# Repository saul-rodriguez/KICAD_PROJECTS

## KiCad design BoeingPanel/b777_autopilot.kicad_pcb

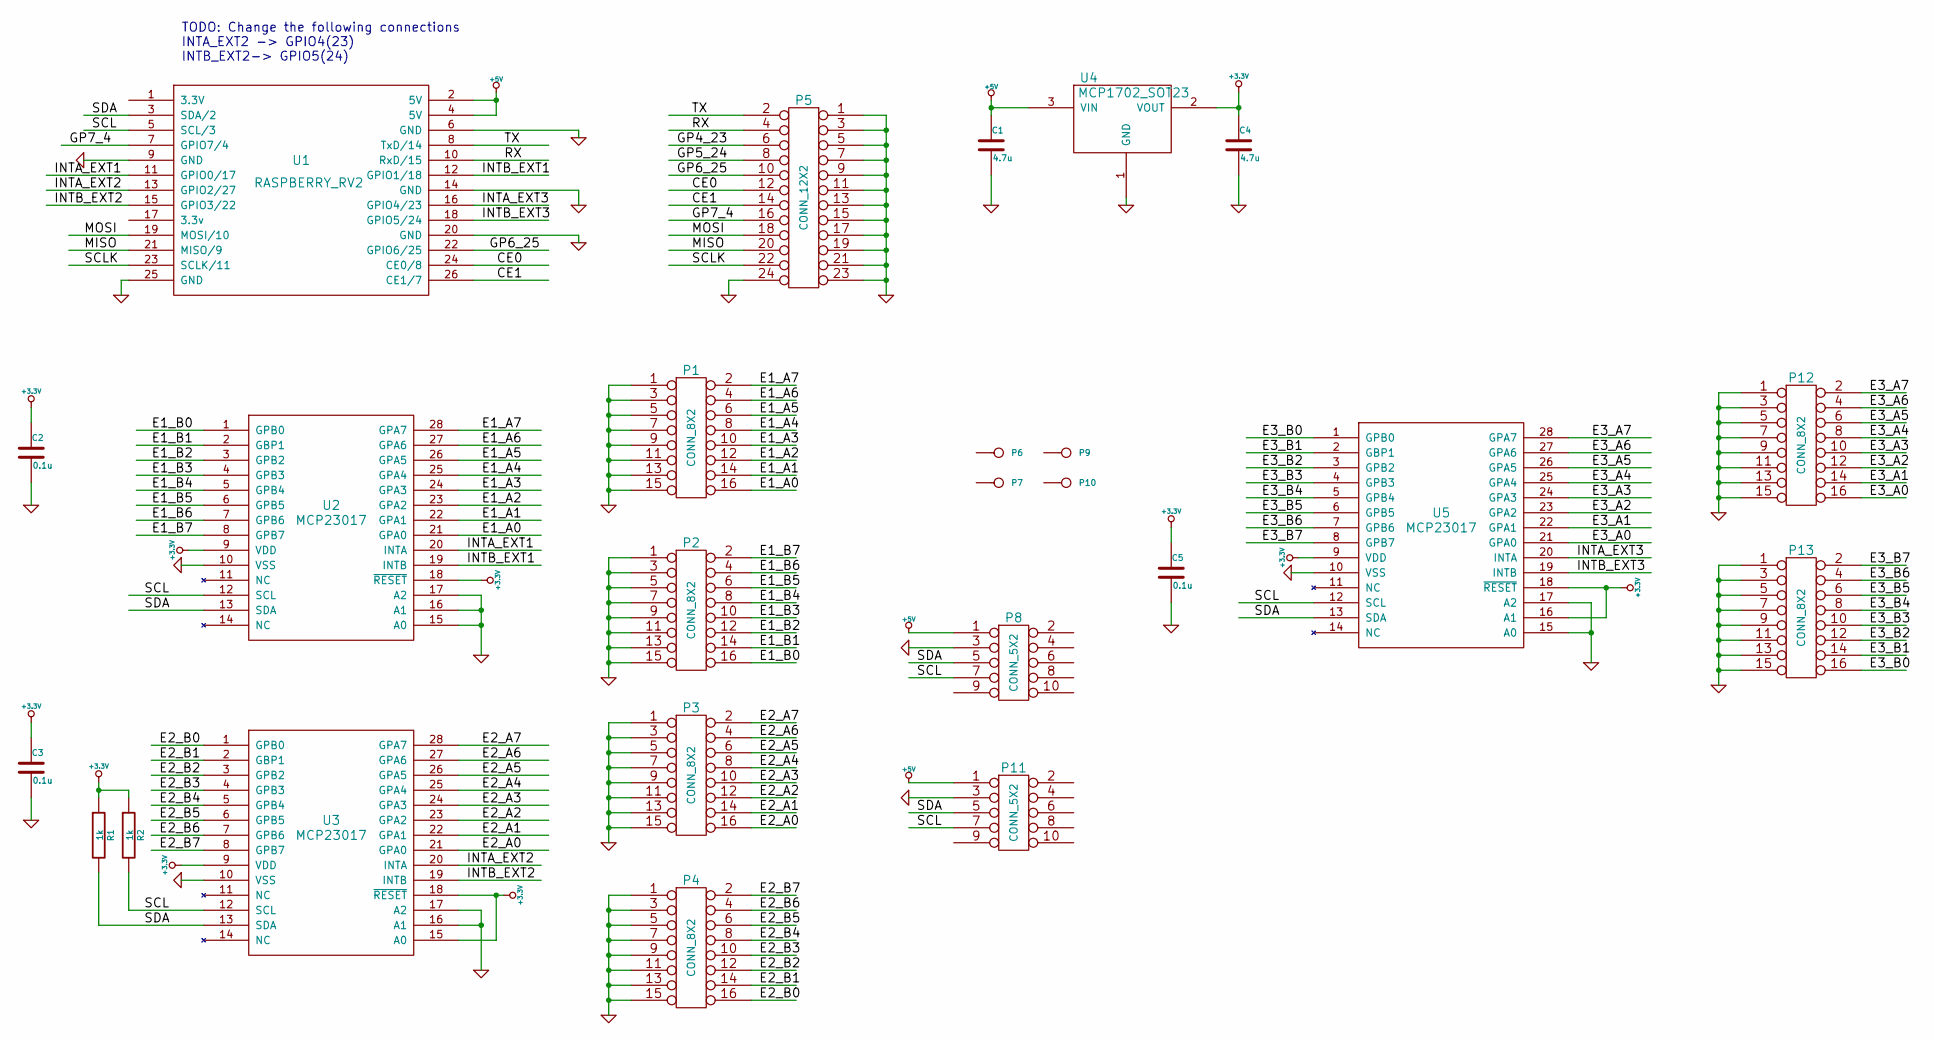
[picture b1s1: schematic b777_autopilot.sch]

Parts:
C1, C4: 4.7u
C2, C3, C5: 0.1u
P1, P2, P3, P4, P12, P13: CONN_8X2
P5: CONN_12X2
P6, P7, P9, P10: CONN_1
P8, P11: CONN_5X2
R1, R2: 1k
U1: RASPBERRY_RV2
U2, U3, U5: MCP23017
U4: MCP1702_SOT23

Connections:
+3.3V: C2.1, C3.1, C4.1, C5.1, R1.1, R2.1, U2.9 (VDD), U2.18 (~RESET), U3.9 (VDD), U3.15 (A0), U3.18 (~RESET), U4.2 (VOUT), U5.9 (VDD), U5.16 (A1), U5.18 (~RESET)
+5V: C1.1, P8.1, P11.1, U1.2 (5V), U1.4 (5V), U4.3 (VIN)
/CE0: P5.12, U1.24 (CE0/8)
/CE1: P5.14, U1.26 (CE1/7)
/E1_A0: P1.16, U2.21 (GPA0)
/E1_A1: P1.14, U2.22 (GPA1)
/E1_A2: P1.12, U2.23 (GPA2)
/E1_A3: P1.10, U2.24 (GPA3)
/E1_A4: P1.8, U2.25 (GPA4)
/E1_A5: P1.6, U2.26 (GPA5)
/E1_A6: P1.4, U2.27 (GPA6)
/E1_A7: P1.2, U2.28 (GPA7)
/E1_B0: P2.16, U2.1 (GPB0)
/E1_B1: P2.14, U2.2 (GBP1)
/E1_B2: P2.12, U2.3 (GPB2)
/E1_B3: P2.10, U2.4 (GPB3)
/E1_B4: P2.8, U2.5 (GPB4)
/E1_B5: P2.6, U2.6 (GPB5)
/E1_B6: P2.4, U2.7 (GPB6)
/E1_B7: P2.2, U2.8 (GPB7)
/E2_A0: P3.16, U3.21 (GPA0)
/E2_A1: P3.14, U3.22 (GPA1)
/E2_A2: P3.12, U3.23 (GPA2)
/E2_A3: P3.10, U3.24 (GPA3)
/E2_A4: P3.8, U3.25 (GPA4)
/E2_A5: P3.6, U3.26 (GPA5)
/E2_A6: P3.4, U3.27 (GPA6)
/E2_A7: P3.2, U3.28 (GPA7)
/E2_B0: P4.16, U3.1 (GPB0)
/E2_B1: P4.14, U3.2 (GBP1)
/E2_B2: P4.12, U3.3 (GPB2)
/E2_B3: P4.10, U3.4 (GPB3)
/E2_B4: P4.8, U3.5 (GPB4)
/E2_B5: P4.6, U3.6 (GPB5)
/E2_B6: P4.4, U3.7 (GPB6)
/E2_B7: P4.2, U3.8 (GPB7)
/E3_A0: P12.16, U5.21 (GPA0)
/E3_A1: P12.14, U5.22 (GPA1)
/E3_A2: P12.12, U5.23 (GPA2)
/E3_A3: P12.10, U5.24 (GPA3)
/E3_A4: P12.8, U5.25 (GPA4)
/E3_A5: P12.6, U5.26 (GPA5)
/E3_A6: P12.4, U5.27 (GPA6)
/E3_A7: P12.2, U5.28 (GPA7)
/E3_B0: P13.16, U5.1 (GPB0)
/E3_B1: P13.14, U5.2 (GBP1)
/E3_B2: P13.12, U5.3 (GPB2)
/E3_B3: P13.10, U5.4 (GPB3)
/E3_B4: P13.8, U5.5 (GPB4)
/E3_B5: P13.6, U5.6 (GPB5)
/E3_B6: P13.4, U5.7 (GPB6)
/E3_B7: P13.2, U5.8 (GPB7)
/GP4_23: P5.6
/GP5_24: P5.8
/GP6_25: P5.10, U1.22 (GPIO6/25)
/GP7_4: P5.16, U1.7 (GPIO7/4)
/INTA_EXT1: U1.11 (GPIO0/17), U2.20 (INTA)
/INTA_EXT2: U1.13 (GPIO2/27), U3.20 (INTA)
/INTA_EXT3: U1.16 (GPIO4/23), U5.20 (INTA)
/INTB_EXT1: U1.12 (GPIO1/18), U2.19 (INTB)
/INTB_EXT2: U1.15 (GPIO3/22), U3.19 (INTB)
/INTB_EXT3: U1.18 (GPIO5/24), U5.19 (INTB)
/MISO: P5.20, U1.21 (MISO/9)
/MOSI: P5.18, U1.19 (MOSI/10)
/RX: P5.4, U1.10 (RxD/15)
/SCL: P8.7, P11.7, R2.2, U1.5 (SCL/3), U2.12 (SCL), U3.12 (SCL), U5.12 (SCL)
/SCLK: P5.22, U1.23 (SCLK/11)
/SDA: P8.5, P11.5, R1.2, U1.3 (SDA/2), U2.13 (SDA), U3.13 (SDA), U5.13 (SDA)
/TX: P5.2, U1.8 (TxD/14)
GND: C1.2, C2.2, C3.2, C4.2, C5.2, P1.1, P1.3, P1.5, P1.7, P1.9, P1.11, P1.13, P1.15, P2.1, P2.3, P2.5, P2.7, P2.9, P2.11, P2.13, P2.15, P3.1, P3.3, P3.5, P3.7, P3.9, P3.11, P3.13, P3.15, P4.1, P4.3, P4.5, P4.7, P4.9, P4.11, P4.13, P4.15, P5.1, P5.3, P5.5, P5.7, P5.9, P5.11, P5.13, P5.15, P5.17, P5.19, P5.21, P5.23, P5.24, P8.3, P11.3, P12.1, P12.3, P12.5, P12.7, P12.9, P12.11, P12.13, P12.15, P13.1, P13.3, P13.5, P13.7, P13.9, P13.11, P13.13, P13.15, U1.6 (GND), U1.9 (GND), U1.14 (GND), U1.20 (GND), U1.25 (GND), U2.10 (VSS), U2.15 (A0), U2.16 (A1), U2.17 (A2), U3.10 (VSS), U3.16 (A1), U3.17 (A2), U4.1 (GND), U5.10 (VSS), U5.15 (A0), U5.17 (A2)

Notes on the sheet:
TODO: Change the following connections INTA_EXT2 -> GPIO4(23) INTB_EXT2-> GPIO5(24)

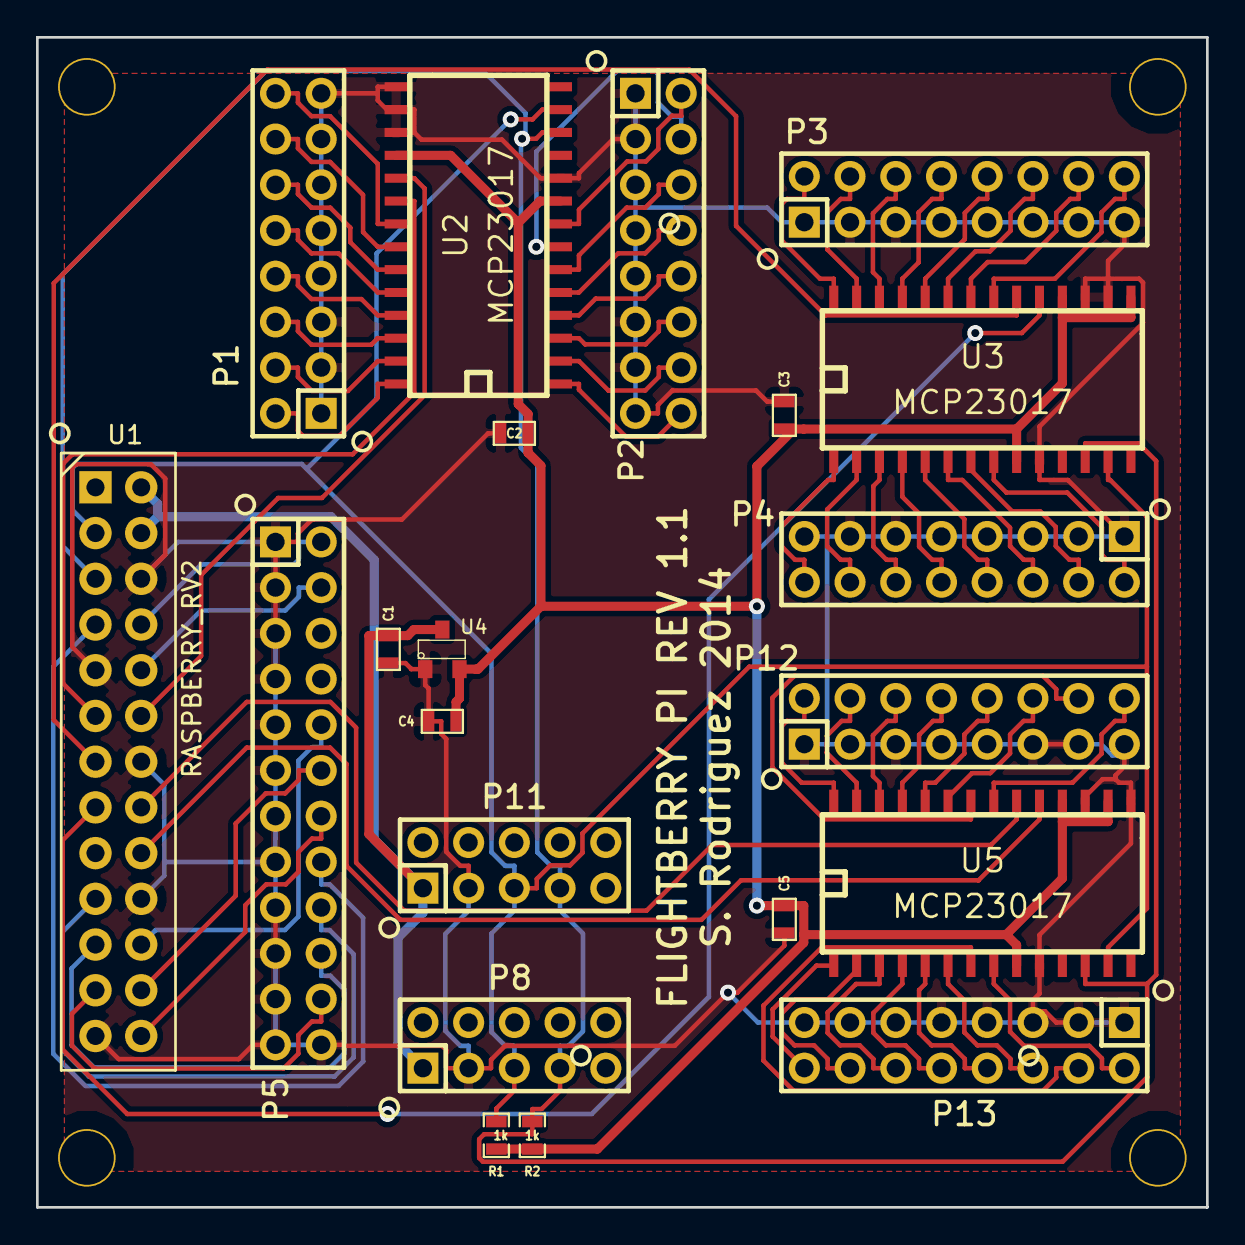
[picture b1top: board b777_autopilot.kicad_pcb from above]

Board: 2 copper layers, 65.0 x 65.0 mm, 25 parts (0 on the bottom side), 68 nets.

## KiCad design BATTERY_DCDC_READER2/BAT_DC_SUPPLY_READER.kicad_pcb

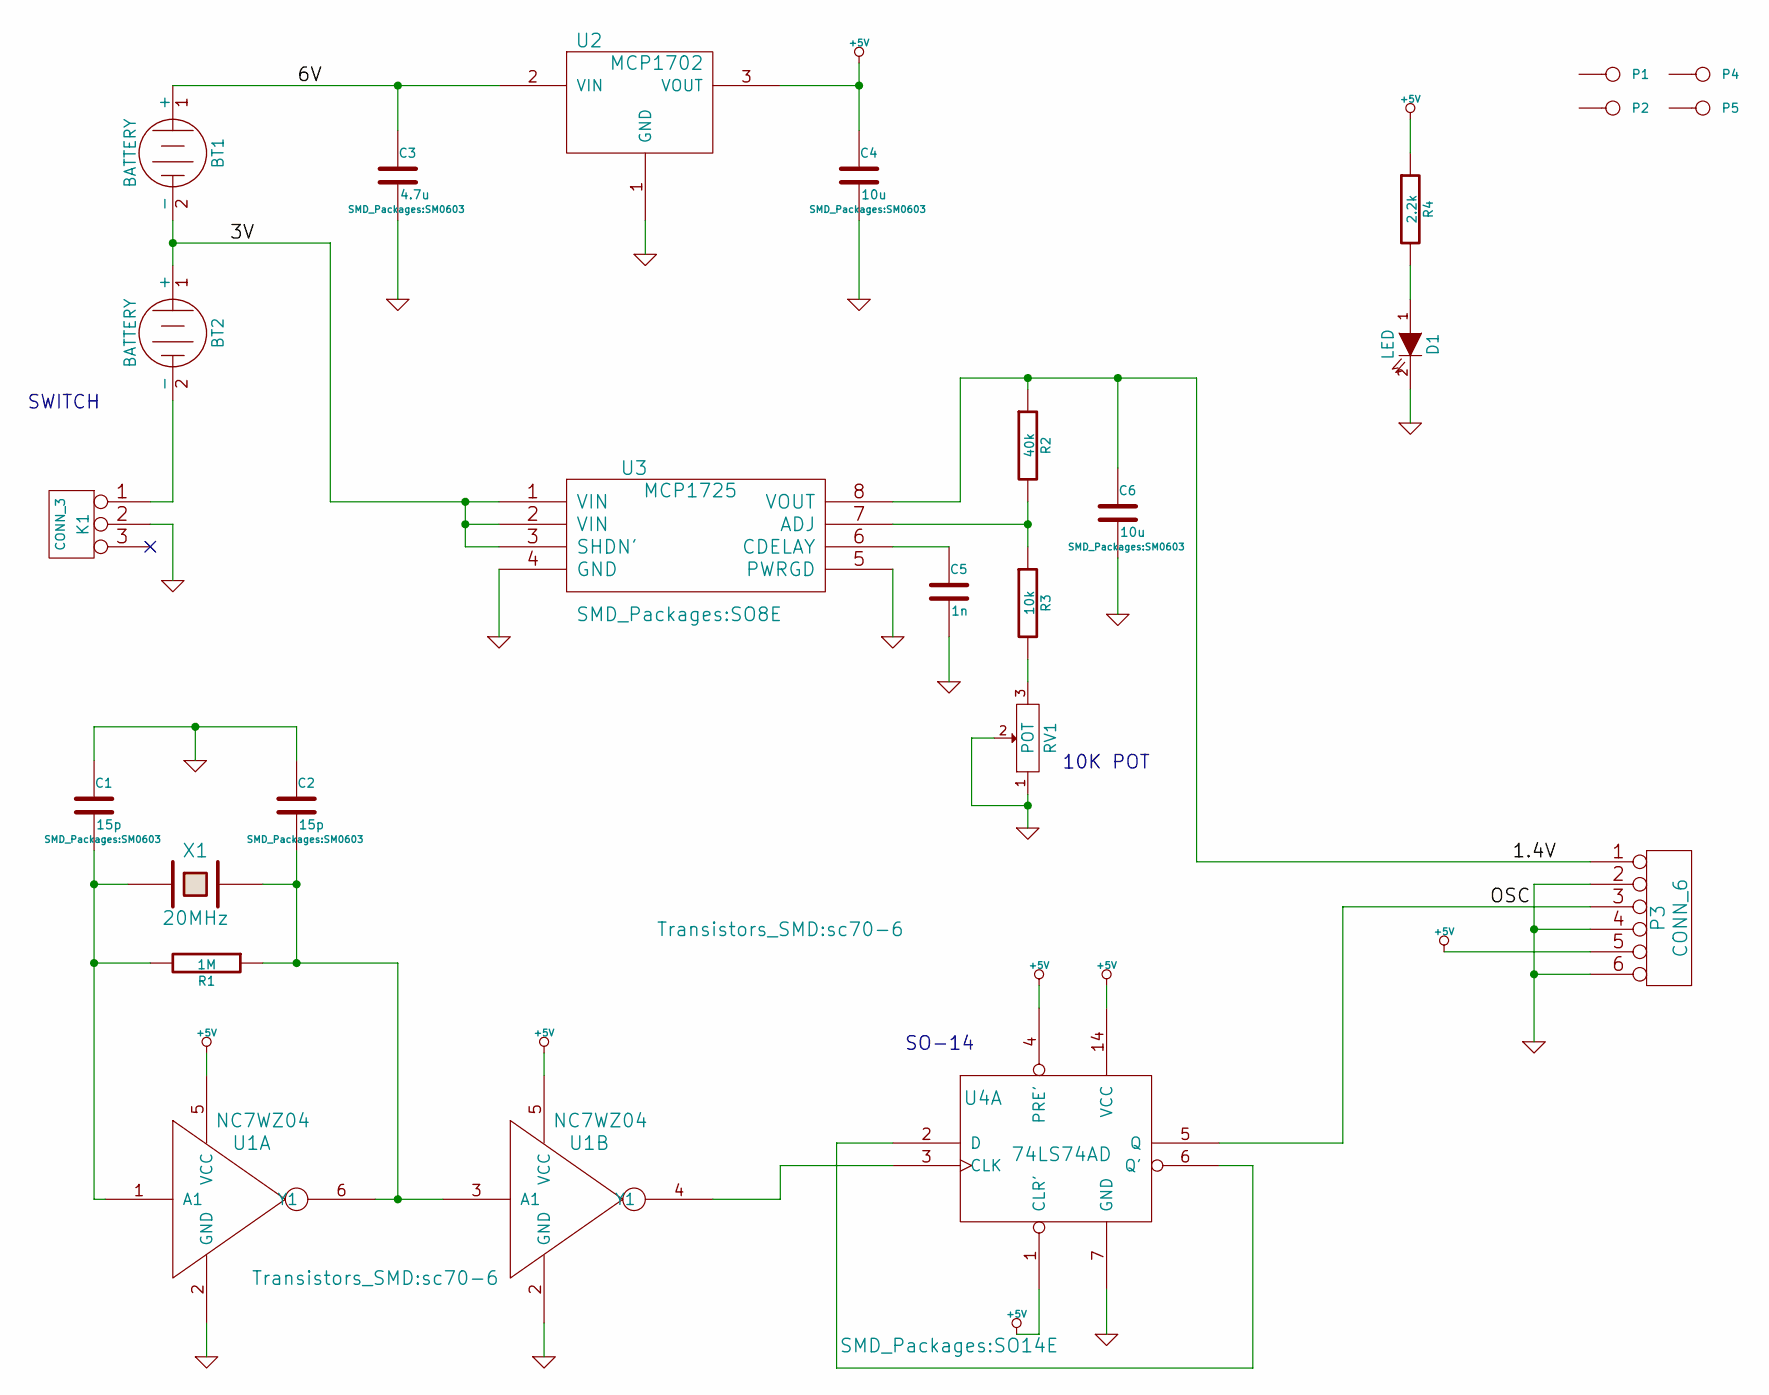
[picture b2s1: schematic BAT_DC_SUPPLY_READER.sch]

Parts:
BT1, BT2: BATTERY; CR123A
C1, C2: 15p; SM0603
C3: 4.7u; SM0603
C4, C6: 10u; SM0603
C5: 1n; SM0603
D1: LED; SM1206
K1: CONN_3; Pin_Header_Straight_1x03
P1, P2, P4, P5: CONN_1; Mhole
P3: CONN_6; Pin_Header_Straight_1x06
R1: 1M; SM0603
R2: 40k; SM0603
R3: 10k; SM0603
R4: 2.2k; SM0603
RV1: POT; R_POT_DIP
U1: NC7WZ04; sc70-6
U2: MCP1702; sot89
U3: MCP1725; SO8E
U4: 74LS74AD; SO14E
X1: 20MHz; Crystal_HC49-U_Vertical

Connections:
+5V: C4.1, P3.5, R4.1, U1.5 (VCC), U2.3 (VOUT), U4.1 (CLR'), U4.4 (PRE'), U4.14 (VCC)
/1.4V: C6.1, P3.1, R2.1, U3.8 (VOUT)
/3V: BT1.2 (-), BT2.1 (+), U3.1 (VIN), U3.2 (VIN), U3.3 (SHDN')
/6V: BT1.1 (+), C3.1, U2.2 (VIN)
/OSC: P3.3, U4.5 (Q)
GND: C1.1, C2.1, C3.2, C4.2, C5.2, C6.2, D1.2 (K), K1.2 (PM), P3.2, P3.4, P3.6, RV1.1, RV1.2, U1.2 (GND), U2.1 (GND), U3.4 (GND), U3.5 (PWRGD), U4.7 (GND)
unnamed: BT2.2 (-), K1.1
unnamed: C1.2, R1.2, U1.1 (A1), X1.1
unnamed: C2.2, R1.1, U1.3 (A1), U1.6 (Y1), X1.2
unnamed: C5.1, U3.6 (CDELAY)
unnamed: D1.1 (A), R4.2
unnamed: R2.2, R3.1, U3.7 (ADJ)
unnamed: R3.2, RV1.3
unnamed: U1.4 (Y1), U4.3 (CLK)
unnamed: U4.2 (D), U4.6 (Q')

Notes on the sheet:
SWITCH
10K POT
SO-14

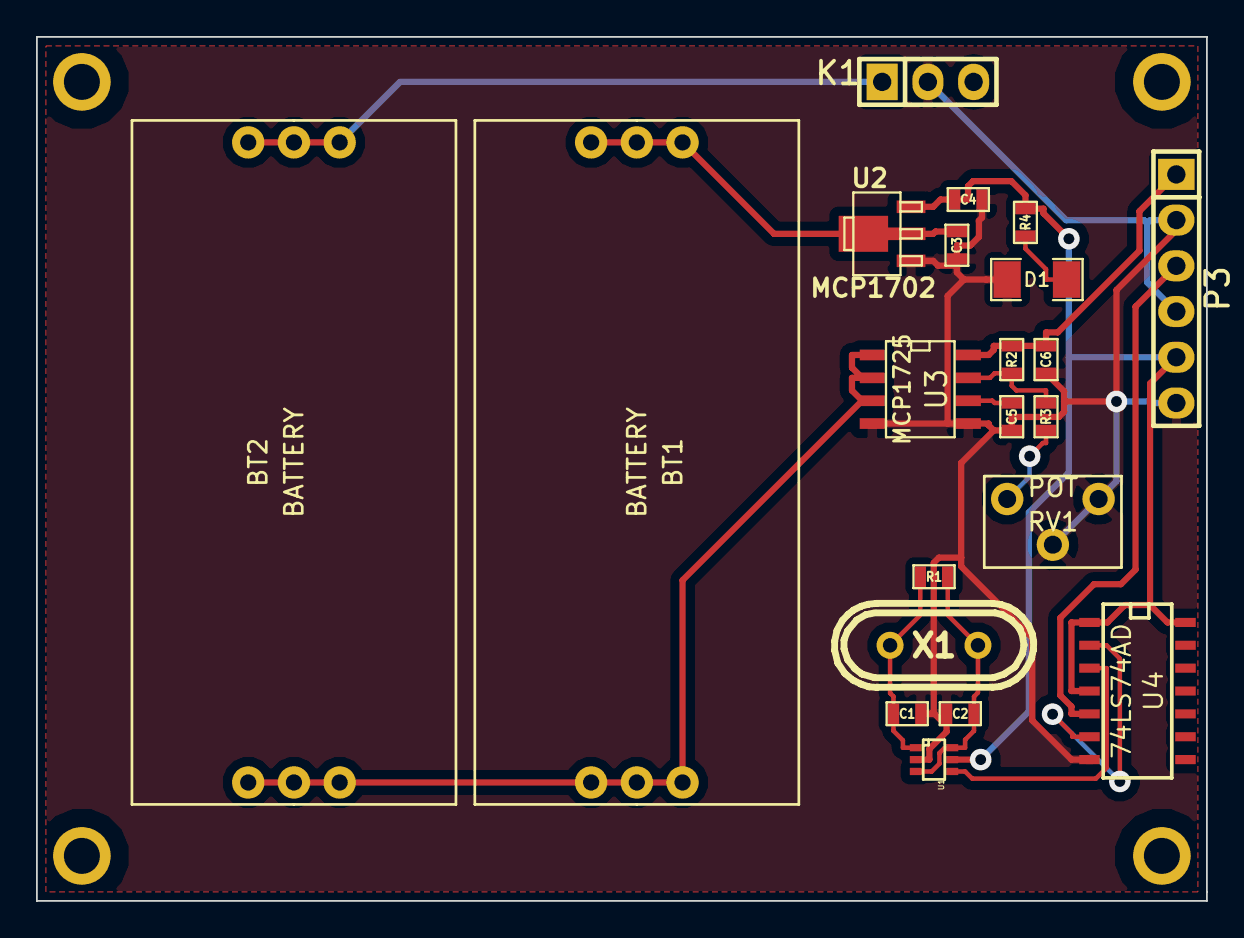
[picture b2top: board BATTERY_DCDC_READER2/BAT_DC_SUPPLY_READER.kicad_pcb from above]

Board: 2 copper layers, 65.0 x 48.0 mm, 25 parts (0 on the bottom side), 15 nets.

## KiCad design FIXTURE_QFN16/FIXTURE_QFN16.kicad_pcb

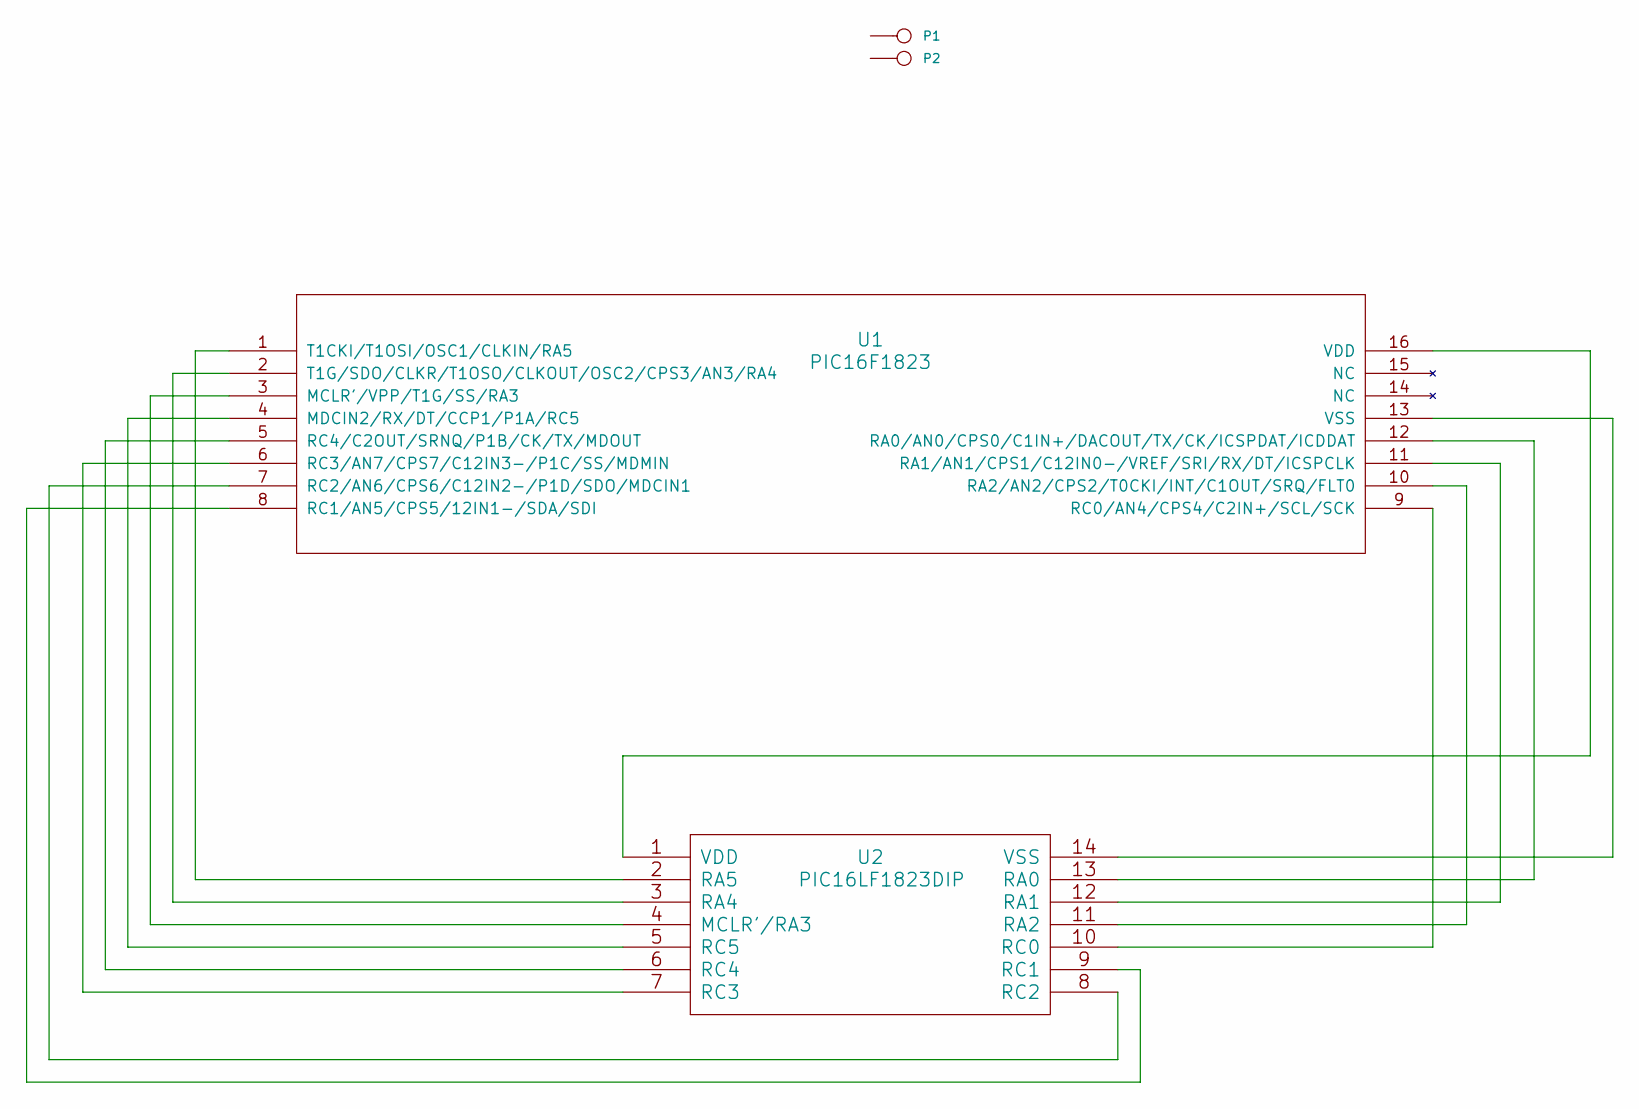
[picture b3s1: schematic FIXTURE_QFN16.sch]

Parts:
P1, P2: CONN_1
U1: PIC16F1823
U2: PIC16LF1823DIP

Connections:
unnamed: U1.1 (T1CKI/T1OSI/OSC1/CLKIN/RA5), U2.2 (RA5)
unnamed: U1.2 (T1G/SDO/CLKR/T1OSO/CLKOUT/OSC2/CPS3/AN3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), U2.3 (RA4)
unnamed: U1.3 (MCLR'/VPP/T1G/SS/RA3), U2.4 (MCLR'/RA3)
unnamed: U1.4 (MDCIN2/RX/DT/CCP1/P1A/RC5), U2.5 (RC5)
unnamed: U1.5 (RC4/C2OUT/SRNQ/P1B/CK/TX/MDOUT), U2.6 (RC4)
unnamed: U1.6 (RC3/AN7/CPS7/C12IN3-/P1C/SS/MDMIN), U2.7 (RC3)
unnamed: U1.7 (RC2/AN6/CPS6/C12IN2-/P1D/SDO/MDCIN1), U2.8 (RC2)
unnamed: U1.8 (RC1/AN5/CPS5/12IN1-/SDA/SDI), U2.9 (RC1)
unnamed: U1.9 (RC0/AN4/CPS4/C2IN+/SCL/SCK), U2.10 (RC0)
unnamed: U1.10 (RA2/AN2/CPS2/T0CKI/INT/C1OUT/SRQ/FLT0), U2.11 (RA2)
unnamed: U1.11 (RA1/AN1/CPS1/C12IN0-/VREF/SRI/RX/DT/ICS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), U2.12 (RA1)
unnamed: U1.12 (RA0/AN0/CPS0/C1IN+/DACOUT/TX/CK/ICSPDAT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), U2.13 (RA0)
unnamed: U1.13 (VSS), U2.14 (VSS)
unnamed: U1.16 (VDD), U2.1 (VDD)

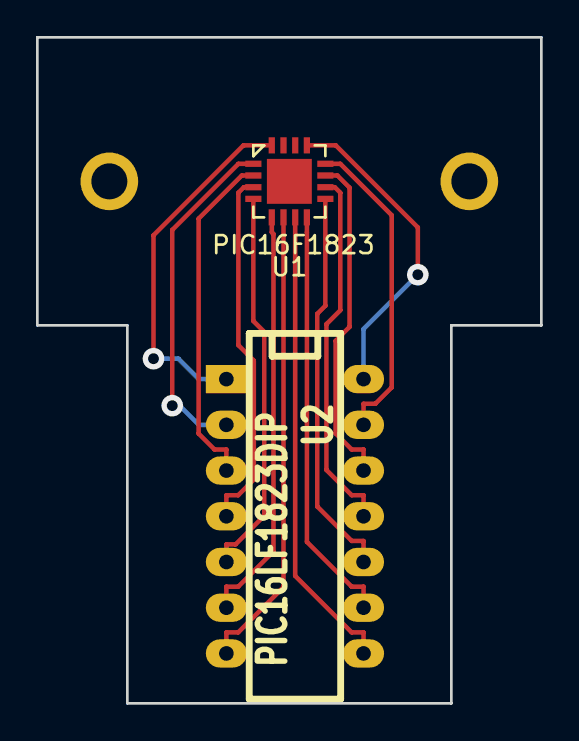
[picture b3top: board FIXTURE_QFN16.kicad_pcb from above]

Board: 2 copper layers, 28.0 x 37.0 mm, 4 parts (0 on the bottom side), 14 nets.

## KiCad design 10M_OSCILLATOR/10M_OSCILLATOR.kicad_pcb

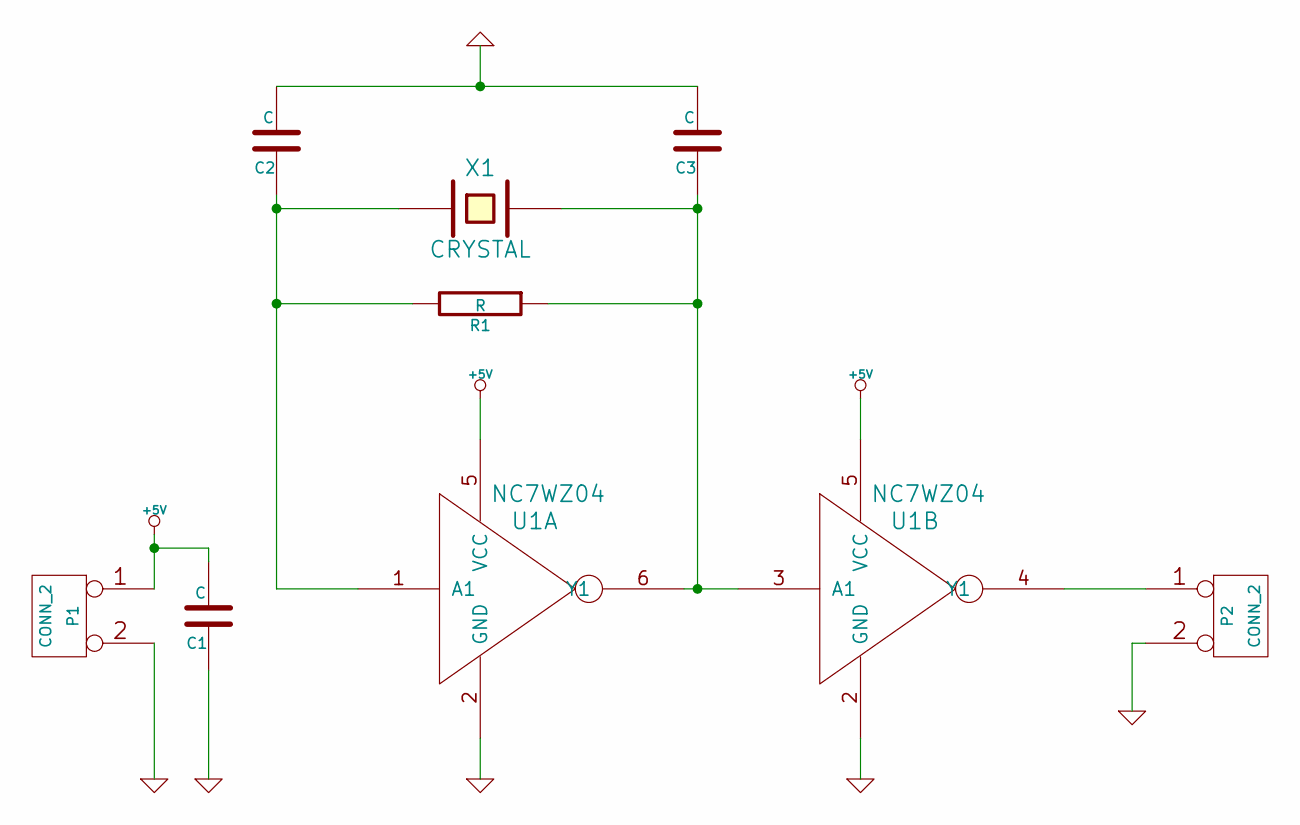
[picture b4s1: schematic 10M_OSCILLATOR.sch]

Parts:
C1, C2, C3: C
P1, P2: CONN_2
R1: R
U1: NC7WZ04
X1: CRYSTAL

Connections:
+5V: C1.2, P1.1, U1.5 (VCC)
GND: C1.1, C2.2, C3.2, P1.2 (PM), P2.2 (PM), U1.2 (GND)
unnamed: P2.1, U1.4 (Y1)
unnamed: C2.1, R1.2, U1.1 (A1), X1.1
unnamed: C3.1, R1.1, U1.3 (A1), U1.6 (Y1), X1.2

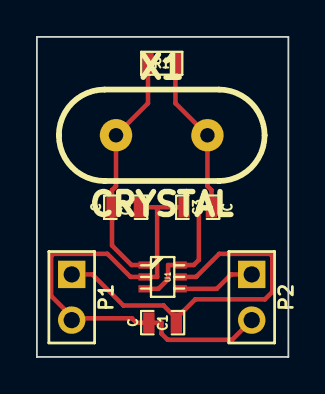
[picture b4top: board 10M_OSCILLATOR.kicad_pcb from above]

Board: 2 copper layers, 14.0 x 17.8 mm, 8 parts (0 on the bottom side), 5 nets.

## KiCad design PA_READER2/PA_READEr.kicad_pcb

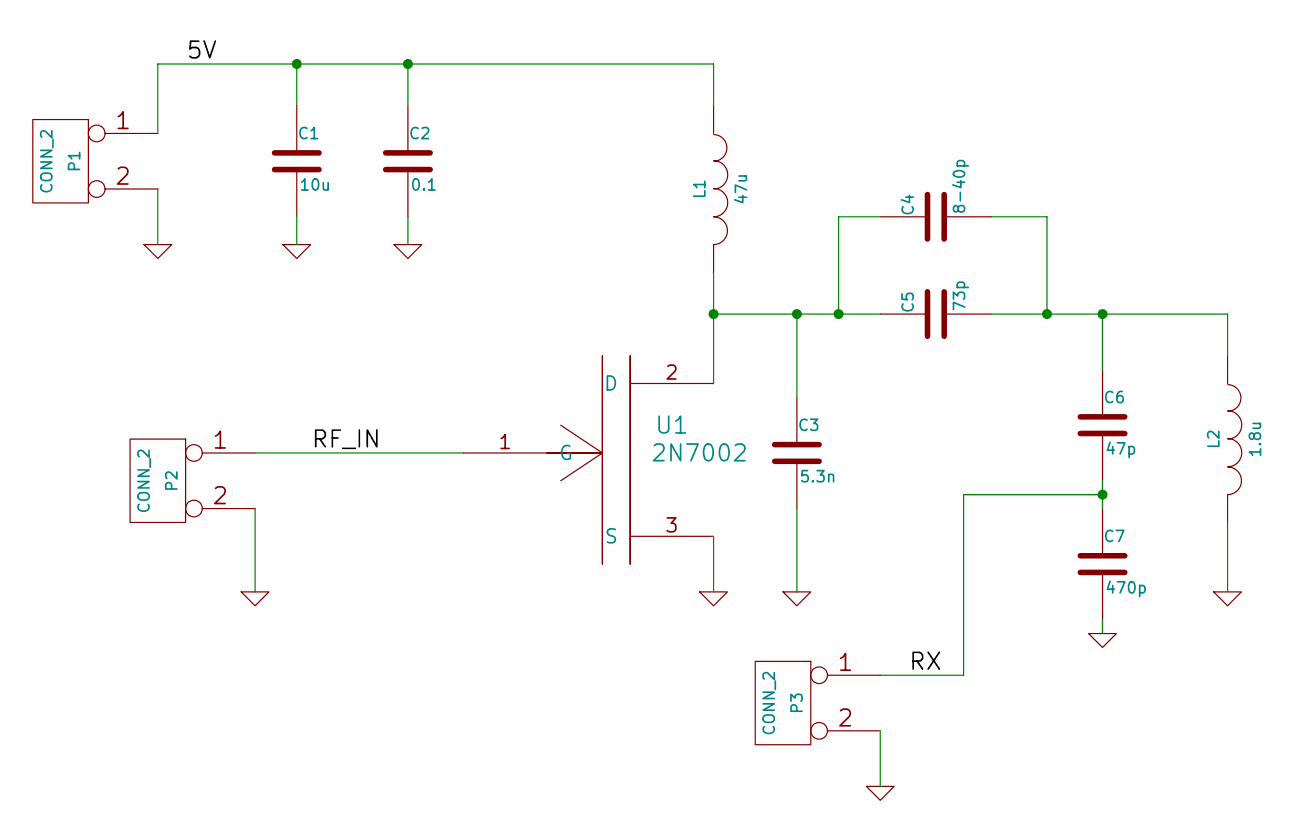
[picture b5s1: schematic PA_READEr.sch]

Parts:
C1: 10u
C2: 0.1
C3: 5.3n
C4: 8-40p
C5: 73p
C6: 47p
C7: 470p
L1: 47u
L2: 1.8u
P1, P2, P3: CONN_2
U1: 2N7002

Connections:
/5V: C1.1, C2.1, L1.1, P1.1
/RF_IN: P2.1, U1.1 (G)
/RX: C6.2, C7.1, P3.1
GND: C1.2, C2.2, C3.2, C7.2, L2.2, P1.2 (PM), P2.2 (PM), P3.2 (PM), U1.3 (S)
unnamed: C3.1, C4.1, C5.1, L1.2, U1.2 (D)
unnamed: C4.2, C5.2, C6.1, L2.1

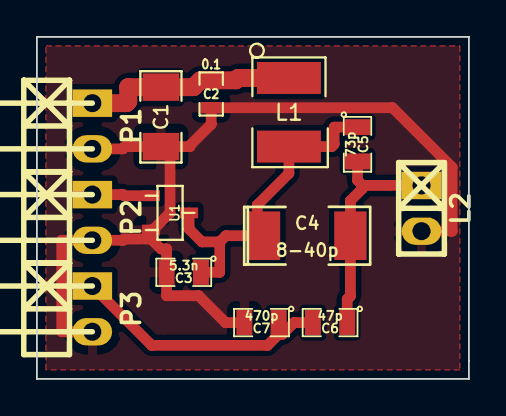
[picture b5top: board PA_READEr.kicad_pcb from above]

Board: 2 copper layers, 24.0 x 19.0 mm, 13 parts (0 on the bottom side), 6 nets.

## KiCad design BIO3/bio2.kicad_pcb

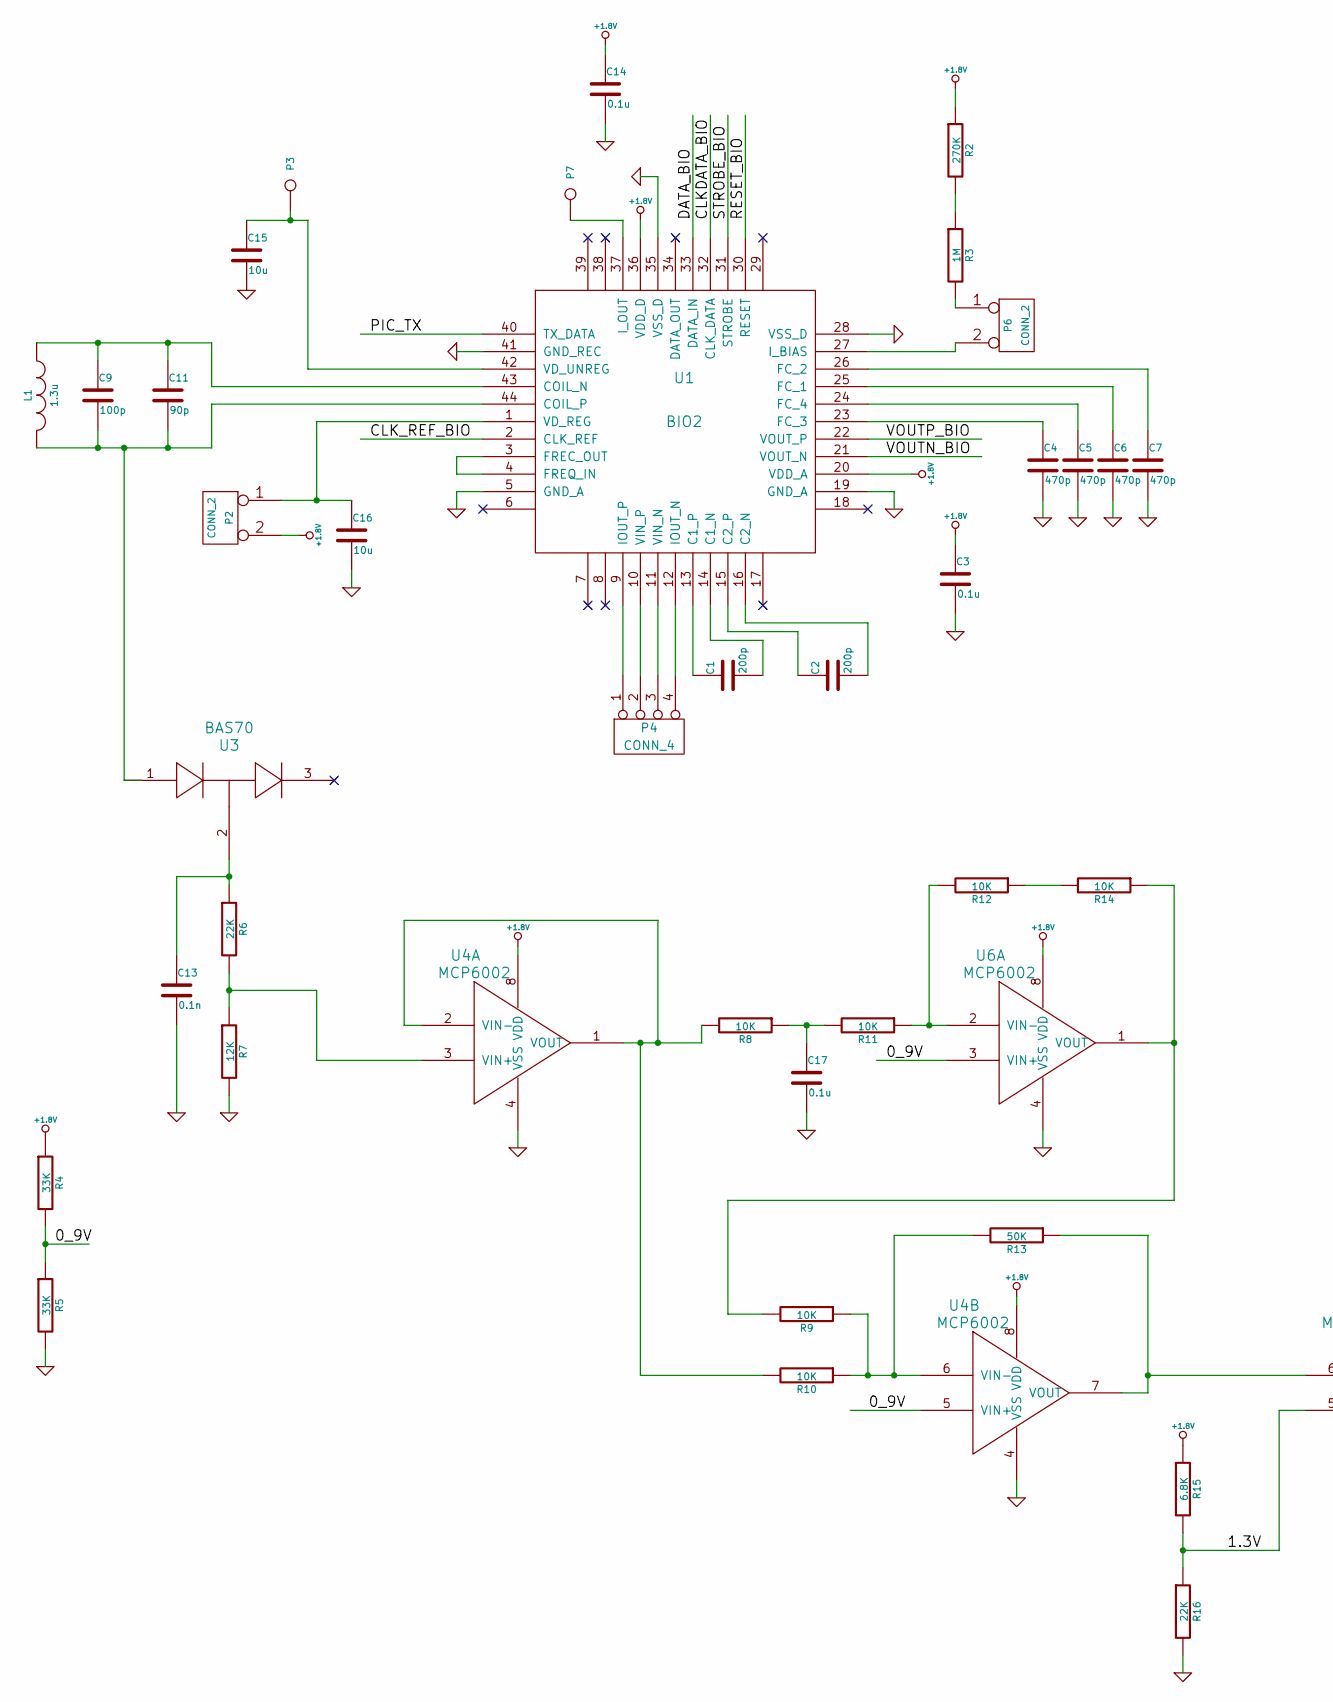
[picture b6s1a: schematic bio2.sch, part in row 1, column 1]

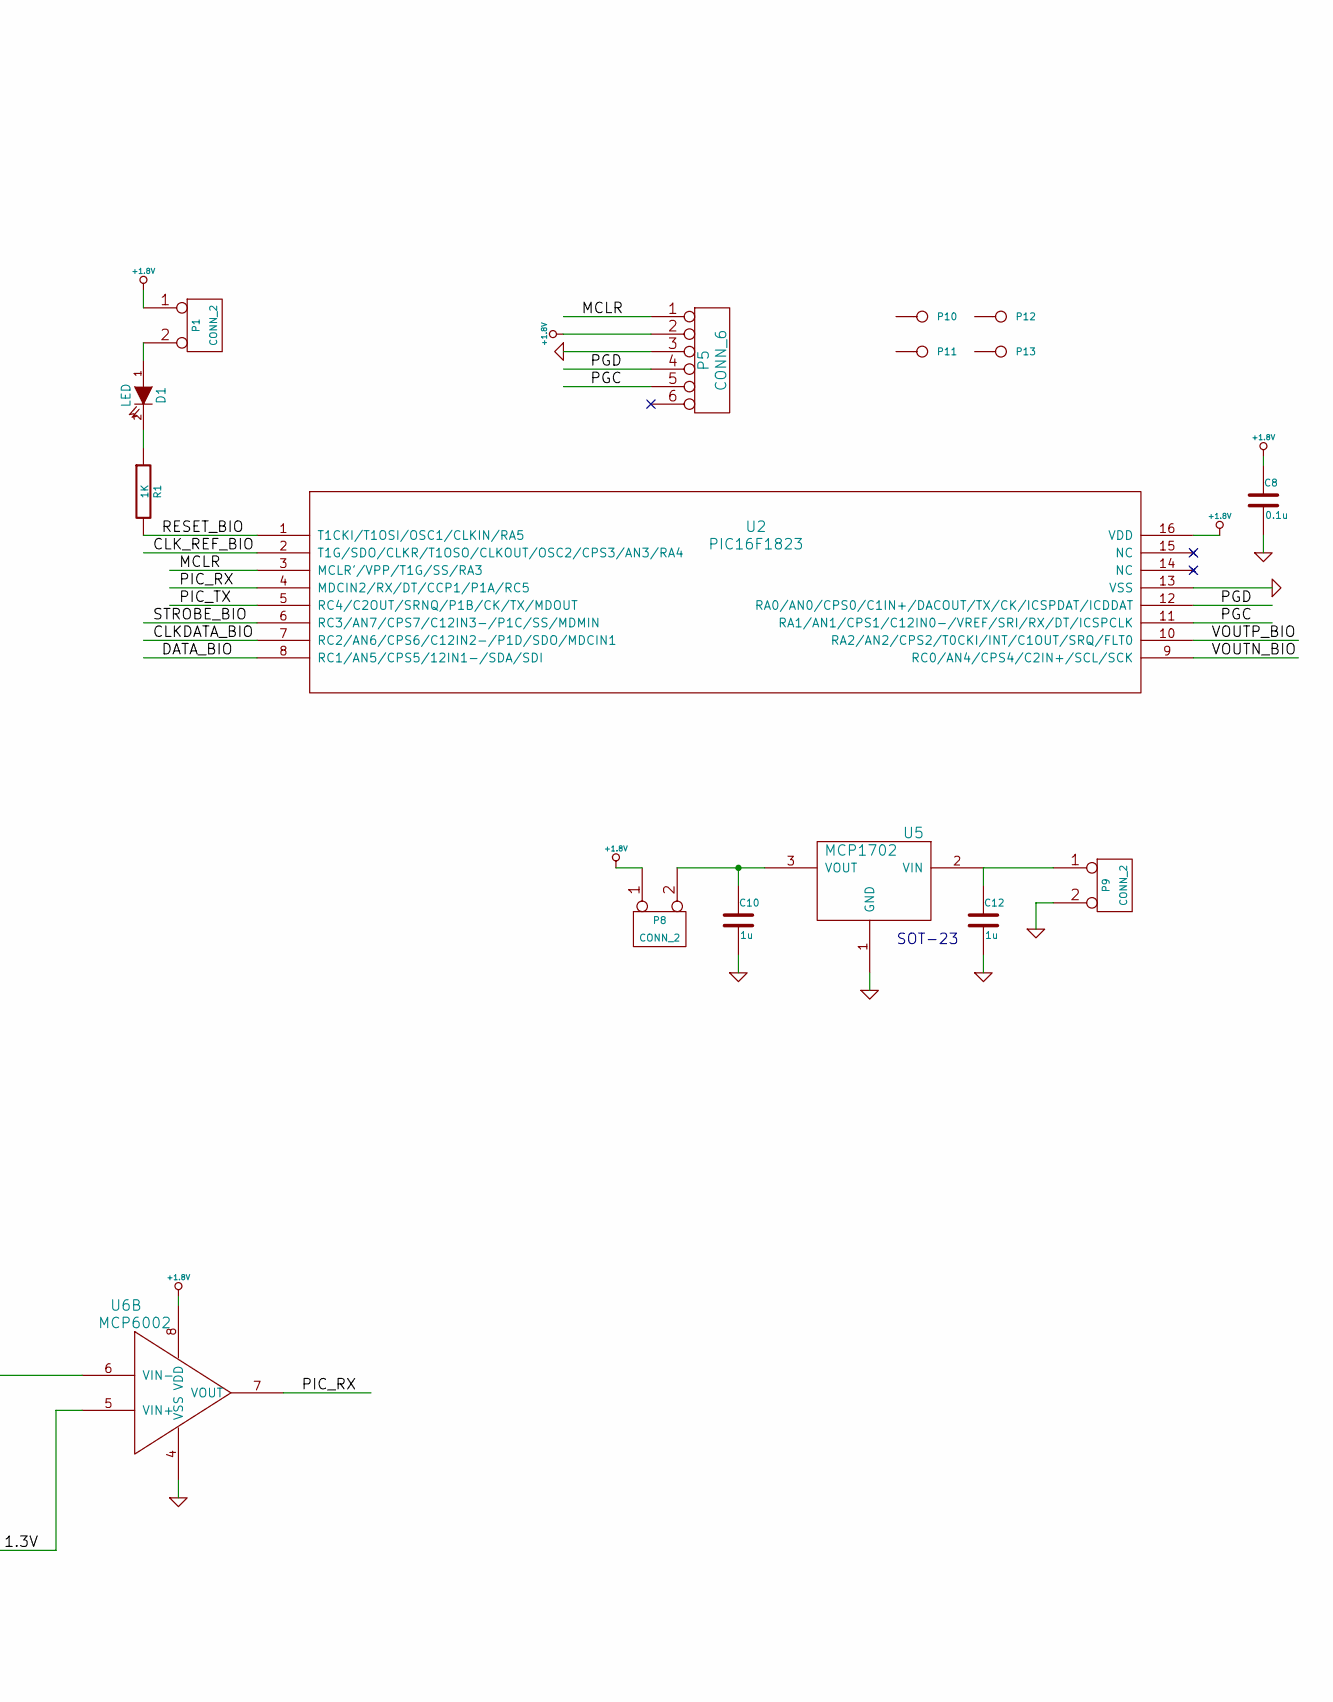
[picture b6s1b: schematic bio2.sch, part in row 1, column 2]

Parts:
C1, C2: 200p; SM0402
C3, C8, C14, C17: 0.1u; SM0402
C4, C5, C6, C7: 470p; SM0402
C9: 100p; SM0402
C10, C12: 1u; SM0402
C11: 90p; SM0402
C13: 0.1n; SM0402
C15, C16: 10u; SM0603
D1: LED; SM1206
L1: 1.3u; Pin_Header_Angled_1x02
P1, P2, P6, P8, P9: CONN_2; Pin_Header_Straight_1x02
P3, P7: CONN_1; Pin_Header_Straight_1x01
P4: CONN_4; Pin_Header_Angled_1x04
P5: CONN_6; Pin_Header_Angled_1x06
P10, P11, P12, P13: CONN_1; Mhole
R1: 1K; SM0402
R2: 270K; SM0402
R3: 1M; SM0402
R4, R5: 33K; SM0402
R6, R16: 22K; SM0402
R7: 12K; SM0402
R8, R9, R10, R11, R12, R14: 10K; SM0402
R13: 50K; SM0402
R15: 6.8K; SM0402
U1: BIO2; PLCC44MS
U2: PIC16F1823; QFN16_MCP
U3: BAS70; SOT23-SPECIAL
U4, U6: MCP6002; DFN8_MC
U5: MCP1702; SOT23-SPECIAL

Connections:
+1.8V: C3.1, C8.1, C14.1, P1.1, P2.2 (PM), P5.2, P8.1, R2.1, R4.1, R15.1, U1.20 (VDD_A), U1.36 (VDD_D), U2.16 (VDD), U4.8 (VDD), U6.8 (VDD)
/0_9V: R4.2, R5.1, U4.5 (VIN+), U6.3 (VIN+)
/1.3V: R15.2, R16.1, U6.5 (VIN+)
/CLKDATA_BIO: U1.32 (CLK_DATA), U2.7 (RC2/AN6/CPS6/C12IN2-/P1D/SDO/MDCIN1)
/CLK_REF_BIO: U1.2 (CLK_REF), U2.2 (T1G/SDO/CLKR/T1OSO/CLKOUT/OSC2/CPS3/AN3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)
/DATA_BIO: U1.33 (DATA_IN), U2.8 (RC1/AN5/CPS5/12IN1-/SDA/SDI)
/MCLR: P5.1, U2.3 (MCLR'/VPP/T1G/SS/RA3)
/PGC: P5.5, U2.11 (RA1/AN1/CPS1/C12IN0-/VREF/SRI/RX/DT/ICS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)
/PGD: P5.4, U2.12 (RA0/AN0/CPS0/C1IN+/DACOUT/TX/CK/ICSPDAT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)
/PIC_RX: U2.4 (MDCIN2/RX/DT/CCP1/P1A/RC5), U6.7 (VOUT)
/PIC_TX: U1.40 (TX_DATA), U2.5 (RC4/C2OUT/SRNQ/P1B/CK/TX/MDOUT)
/RESET_BIO: R1.2, U1.30 (RESET), U2.1 (T1CKI/T1OSI/OSC1/CLKIN/RA5)
/STROBE_BIO: U1.31 (STROBE), U2.6 (RC3/AN7/CPS7/C12IN3-/P1C/SS/MDMIN)
/VOUTN_BIO: U1.21 (VOUT_N), U2.9 (RC0/AN4/CPS4/C2IN+/SCL/SCK)
/VOUTP_BIO: U1.22 (VOUT_P), U2.10 (RA2/AN2/CPS2/T0CKI/INT/C1OUT/SRQ/FLT0)
GND: C3.2, C4.2, C5.2, C6.2, C7.2, C8.2, C10.2, C12.2, C13.2, C14.2, C15.2, C16.2, C17.2, P5.3, P9.2 (PM), R5.2, R7.2, R16.2, U1.5 (GND_A), U1.19 (GND_A), U1.28 (VSS_D), U1.35 (VSS_D), U1.41 (GND_REC), U2.13 (VSS), U4.4 (VSS), U5.1 (GND), U6.4 (VSS)
unnamed: C1.1, U1.13 (C1_P)
unnamed: C1.2, U1.14 (C1_N)
unnamed: C2.1, U1.15 (C2_P)
unnamed: C2.2, U1.16 (C2_N)
unnamed: C4.1, U1.23 (FC_3)
unnamed: C5.1, U1.24 (FC_4)
unnamed: C6.1, U1.25 (FC_1)
unnamed: C7.1, U1.26 (FC_2)
unnamed: C10.1, P8.2 (PM), U5.3 (VOUT)
unnamed: C9.1, C11.1, L1.1, U1.43 (COIL_N)
unnamed: C9.2, C11.2, L1.2, U1.44 (COIL_P), U3.1
unnamed: C12.1, P9.1, U5.2 (VIN)
unnamed: C13.1, R6.1, U3.2
unnamed: C15.1, P3.1, U1.42 (VD_UNREG)
unnamed: C16.1, P2.1, U1.1 (VD_REG)
unnamed: C17.1, R8.1, R11.2
unnamed: D1.1 (A), P1.2 (PM)
unnamed: D1.2 (K), R1.1
unnamed: P4.1, U1.9 (IOUT_P)
unnamed: P4.2, U1.10 (VIN_P)
unnamed: P4.3, U1.11 (VIN_N)
unnamed: P4.4, U1.12 (IOUT_N)
unnamed: P6.1, R3.2
unnamed: P6.2 (PM), U1.27 (I_BIAS)
unnamed: P7.1, U1.37 (I_OUT)
unnamed: R2.2, R3.1
unnamed: R6.2, R7.1, U4.3 (VIN+)
unnamed: R9.1, R10.1, R13.2, U4.6 (VIN-)
unnamed: R8.2, R10.2, U4.1 (VOUT), U4.2 (VIN-)
unnamed: R11.1, R12.2, U6.2 (VIN-)
unnamed: R12.1, R14.2
unnamed: R13.1, U4.7 (VOUT), U6.6 (VIN-)
unnamed: R9.2, R14.1, U6.1 (VOUT)
unnamed: U1.3 (FREC_OUT), U1.4 (FREQ_IN)

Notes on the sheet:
SOT-23
